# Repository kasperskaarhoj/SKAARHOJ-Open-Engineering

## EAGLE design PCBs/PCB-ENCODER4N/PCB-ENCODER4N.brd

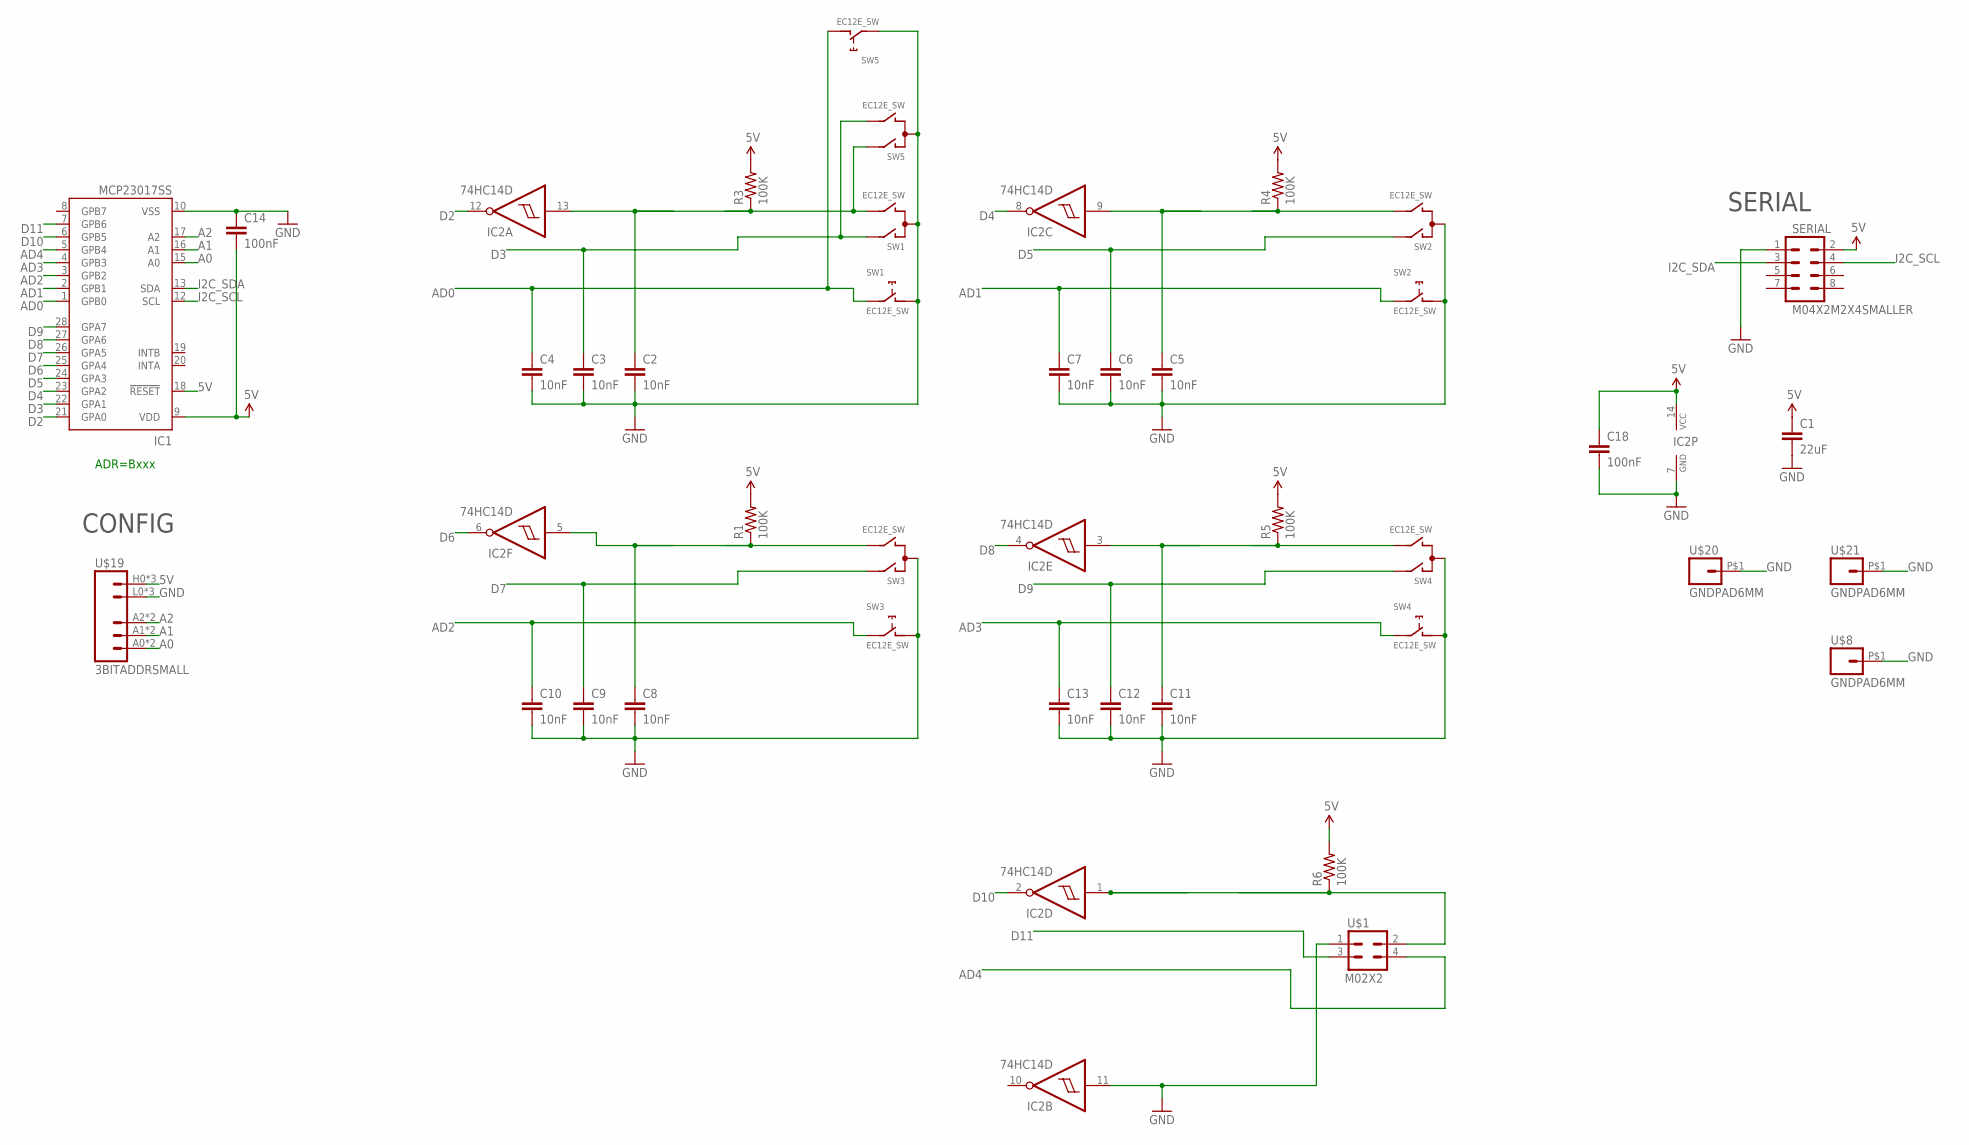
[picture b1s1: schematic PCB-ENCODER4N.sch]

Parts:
C1: 22uF; 0805
C2, C3, C4, C5, C6, C7, C8, C9, C10, C11, C12, C13: 10nF; 0603-CAP
C14, C18: 100nF; 0603-CAP
IC1: MCP23017SS; SSOP28; MPN MCP23017-E/SS
IC2: 74HC14D; SO14
R1, R3, R4, R5, R6: 100K; 0603-RES
SERIAL: M04X2M2X4SMALLER; M2X4SMALLER
SW1, SW2, SW3, SW4, SW5: EC12E_SW; ALPS_EC12E_SW
U$1: M02X2; 2X2
U$8, U$20, U$21: GNDPAD6MM; 3.2MMPAD6MM
U$19: 3BITADDRSMALL; 3BITADDR_SMALL

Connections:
5V: C1.1, C14.2, C18.1, IC1.9 (VDD), IC1.18 (!RESET), IC2.14 (VCC), R1.2, R3.2, R4.2, R5.2, R6.2, SERIAL.2, U$19.H0 (VCC), U$19.H1 (VCC), U$19.H2 (VCC)
A0: IC1.15 (A0), U$19.A0, U$19.AS0 (A0)
A1: IC1.16 (A1), U$19.A1, U$19.AS1 (A1)
A2: IC1.17 (A2), U$19.A2, U$19.AS2 (A2)
AD0: C4.1, IC1.1 (GPB0), SW1.E (2), SW5.D (1)
AD1: C7.1, IC1.2 (GPB1), SW2.E (2)
AD2: C10.1, IC1.3 (GPB2), SW3.E (2)
AD3: C13.1, IC1.4 (GPB3), SW4.E (2)
AD4: IC1.5 (GPB4), U$1.4
D2: IC1.21 (GPA0), IC2.12 (O)
D3: C3.1, IC1.22 (GPA1), SW1.A, SW5.B
D4: IC1.23 (GPA2), IC2.8 (O)
D5: C6.1, IC1.24 (GPA3), SW2.A
D6: IC1.25 (GPA4), IC2.6 (O)
D7: C9.1, IC1.26 (GPA5), SW3.A
D8: IC1.27 (GPA6), IC2.4 (O)
D9: C12.1, IC1.28 (GPA7), SW4.A
D10: IC1.6 (GPB5), IC2.2 (O)
D11: IC1.7 (GPB6), U$1.3
GND: C1.2, C2.2, C3.2, C4.2, C5.2, C6.2, C7.2, C8.2, C9.2, C10.2, C11.2, C12.2, C13.2, C14.1, C18.2, IC1.10 (VSS), IC2.7 (GND), IC2.11 (I), SERIAL.1, SW1.C, SW1.D (1), SW2.C, SW2.D (1), SW3.C, SW3.D (1), SW4.C, SW4.D (1), SW5.C, SW5.E (2), U$1.1, U$8.P$1, U$19.L0 (GND), U$19.L1 (GND), U$19.L2 (GND), U$20.P$1, U$21.P$1
I2C_SCL: IC1.12 (SCL), SERIAL.4
I2C_SDA: IC1.13 (SDA), SERIAL.3
unnamed: IC2.1 (I), R6.1, U$1.2
unnamed: C8.1, IC2.5 (I), R1.1, SW3.B
unnamed: C2.1, IC2.13 (I), R3.1, SW1.B, SW5.A
unnamed: C5.1, IC2.9 (I), R4.1, SW2.B
unnamed: C11.1, IC2.3 (I), R5.1, SW4.B

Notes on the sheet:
SERIAL
ADR=Bxxx
CONFIG

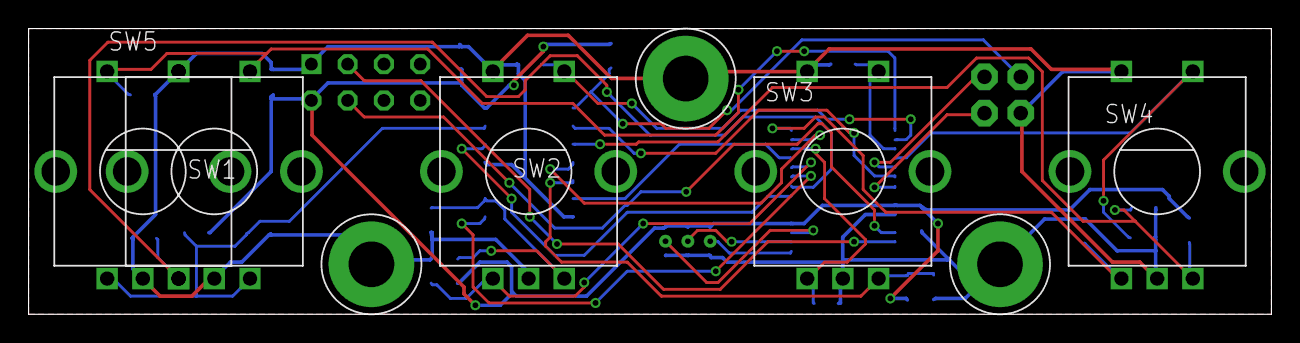
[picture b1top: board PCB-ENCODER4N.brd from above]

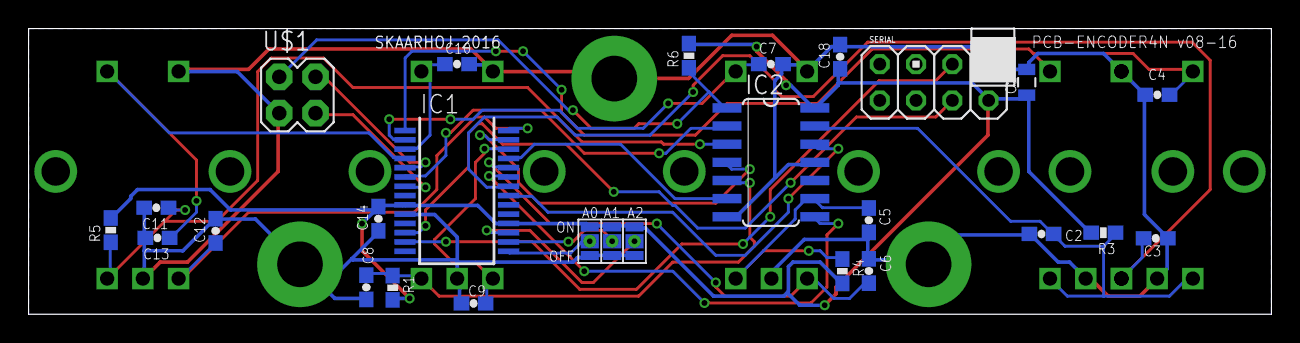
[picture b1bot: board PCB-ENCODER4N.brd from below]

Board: 2 copper layers, 87.0 x 20.0 mm, 33 parts (25 on the bottom side), 27 nets.

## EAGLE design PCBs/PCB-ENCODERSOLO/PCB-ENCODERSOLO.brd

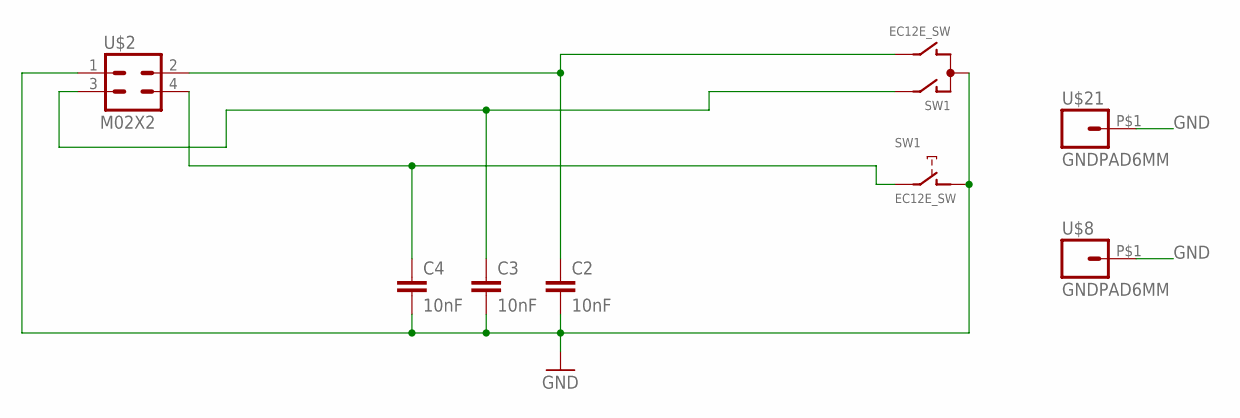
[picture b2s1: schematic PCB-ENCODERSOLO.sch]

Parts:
C2, C3, C4: 10nF; 0603-CAP
SW1: EC12E_SW; ALPS_EC12E_SW
U$2: M02X2; 2X2
U$8, U$21: GNDPAD6MM; 3.2MMPAD6MM

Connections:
AD0: C4.1, SW1.E (2), U$2.4
D3: C3.1, SW1.A, U$2.3
GND: C2.2, C3.2, C4.2, SW1.C, SW1.D (1), U$2.1, U$8.P$1, U$21.P$1
unnamed: C2.1, SW1.B, U$2.2

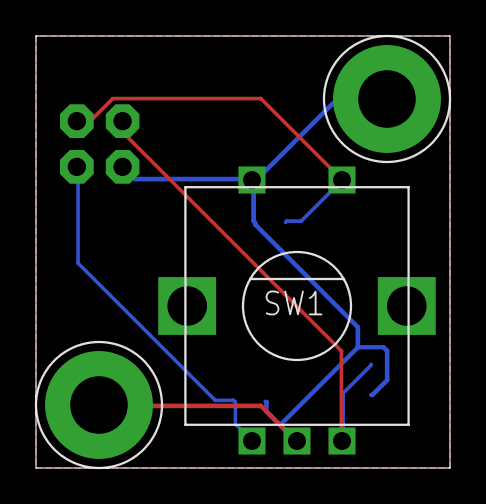
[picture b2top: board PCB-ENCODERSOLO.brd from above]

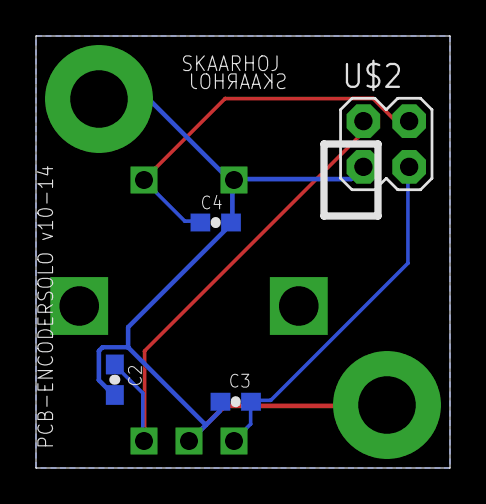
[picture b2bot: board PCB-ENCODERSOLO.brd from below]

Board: 2 copper layers, 23.0 x 24.0 mm, 7 parts (4 on the bottom side), 4 nets.

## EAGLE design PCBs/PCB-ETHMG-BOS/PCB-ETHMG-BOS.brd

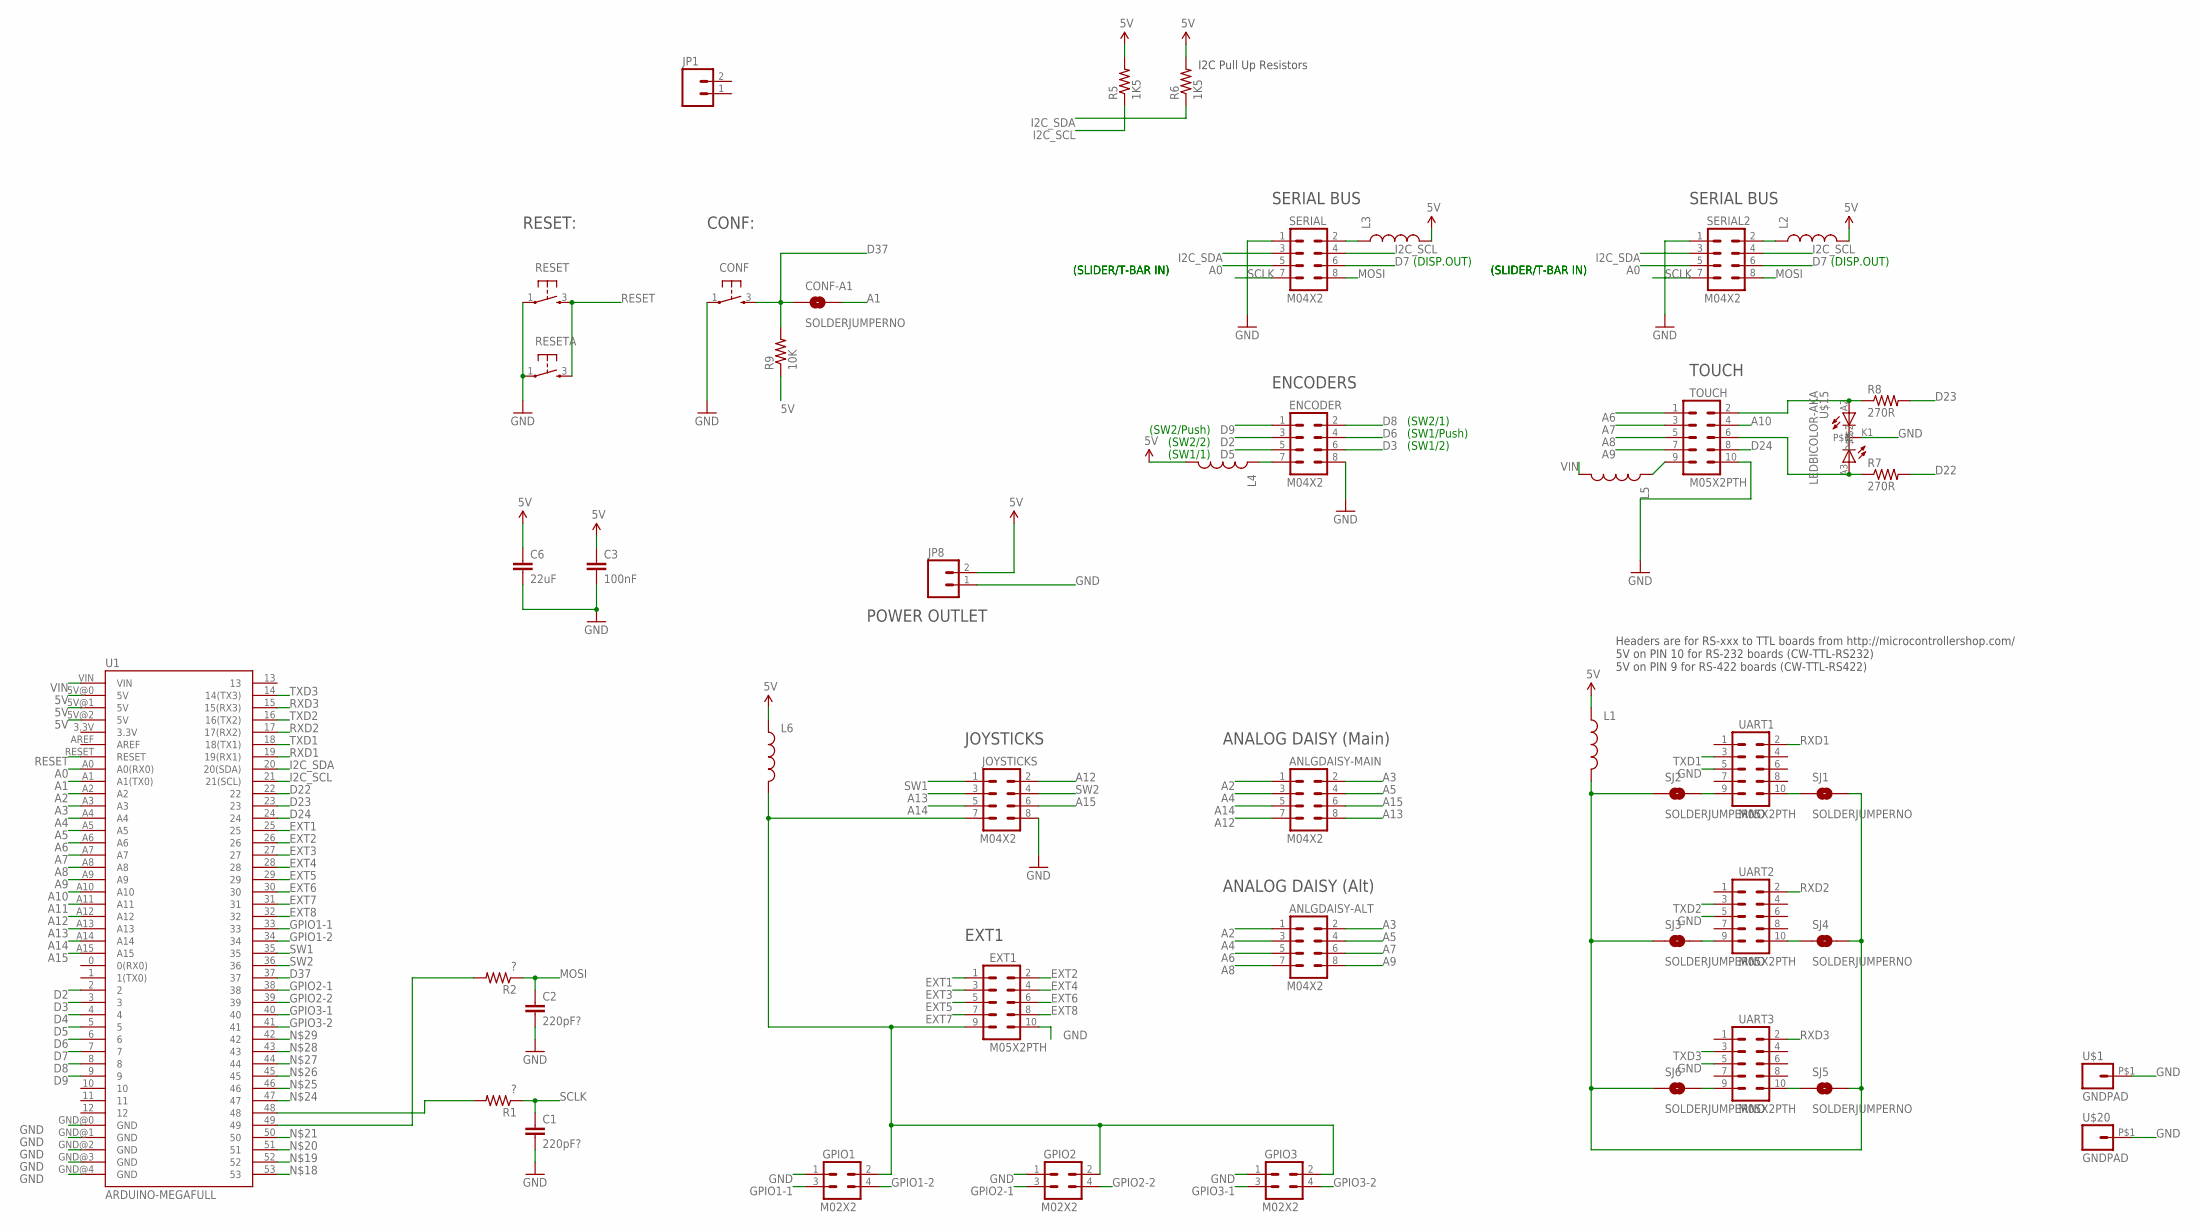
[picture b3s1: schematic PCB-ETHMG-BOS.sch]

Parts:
ANLGDAISY-ALT: M04X2; 2X4
ANLGDAISY-MAIN: M04X2; 2X4
C1, C2: 220pF?; 0603-CAP
C3: 100nF; 0603-CAP
C6: 22uF; 0805
CONF: TAC_SWITCH; PUSHBUTTON
CONF-A1: SOLDERJUMPERNO; SJ_2S-NO
ENCODER: M04X2; 2X4
EXT1: M05X2PTH; AVR_ICSP
GPIO1, GPIO2, GPIO3: M02X2; 2X2
JOYSTICKS: M04X2; 2X4
JP1: M02PTH; 1X02
JP8: M02PTH4; 1X02_XTRA_BIG
L1, L2, L3, L4, L5, L6: INDUCTOR0805; 0805
R1, R2: ?; 0603-RES
R5, R6: 1K5; 0603-RES
R7, R8: 270R; 0603-RES
R9: 10K; 0603-RES
RESET: TAC_SWITCH; PUSHBUTTON
RESETA: TAC_SWITCH; PUSHBUTTON
SERIAL, SERIAL2: M04X2; 2X4
SJ1, SJ2, SJ3, SJ4, SJ5, SJ6: SOLDERJUMPERNO; SJ_2S-NO
TOUCH: M05X2PTH; AVR_ICSP
U1: ARDUINO-MEGAFULL; ARDUINO_MEGA
U$1, U$20: GNDPAD; 3.2MMPAD
U$15: LEDBICOLOR-AKA; LED5MM-BICOLOR
UART1, UART2, UART3: M05X2PTH; AVR_ICSP

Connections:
5V: C3.1, C6.1, JP8.2, L1.1, L2.2, L3.2, L4.2, L6.1, R5.2, R6.2, R9.1, U1.5V@0 (5V), U1.5V@1 (5V), U1.5V@2 (5V)
A0: SERIAL.5, SERIAL2.5, U1.A0 (A0(RX0))
A1: CONF-A1.2, U1.A1 (A1(TX0))
A2: ANLGDAISY-ALT.1, ANLGDAISY-MAIN.1, U1.A2
A3: ANLGDAISY-ALT.2, ANLGDAISY-MAIN.2, U1.A3
A4: ANLGDAISY-ALT.3, ANLGDAISY-MAIN.3, U1.A4
A5: ANLGDAISY-ALT.4, ANLGDAISY-MAIN.4, U1.A5
A6: ANLGDAISY-ALT.5, TOUCH.1, U1.A6
A7: ANLGDAISY-ALT.6, TOUCH.3, U1.A7
A8: ANLGDAISY-ALT.7, TOUCH.5, U1.A8
A9: ANLGDAISY-ALT.8, TOUCH.7, U1.A9
A10: TOUCH.4, U1.A10
A11: U1.A11
A12: ANLGDAISY-MAIN.7, JOYSTICKS.2, U1.A12
A13: ANLGDAISY-MAIN.8, JOYSTICKS.3, U1.A13
A14: ANLGDAISY-MAIN.5, JOYSTICKS.5, U1.A14
A15: ANLGDAISY-MAIN.6, JOYSTICKS.6, U1.A15
D2: ENCODER.3, U1.2
D3: ENCODER.6, U1.3
D4: U1.4
D5: ENCODER.5, U1.5
D6: ENCODER.4, U1.6
D7: SERIAL.6, SERIAL2.6, U1.7
D8: ENCODER.2, U1.8
D9: ENCODER.1, U1.9
D22: R7.2, U1.22
D23: R8.2, U1.23
D24: TOUCH.8, U1.24
D37: CONF.3, CONF-A1.1, R9.2, U1.37
EXT1: EXT1.1, U1.25
EXT2: EXT1.2, U1.26
EXT3: EXT1.3, U1.27
EXT4: EXT1.4, U1.28
EXT5: EXT1.5, U1.29
EXT6: EXT1.6, U1.30
EXT7: EXT1.7, U1.31
EXT8: EXT1.8, U1.32
GND: C1.2, C2.2, C3.2, C6.2, CONF.1, ENCODER.8, EXT1.10, GPIO1.1, GPIO2.1, GPIO3.1, JOYSTICKS.8, JP8.1, RESET.1, RESETA.1, SERIAL.1, SERIAL2.1, TOUCH.10, U1.GND@0 (GND), U1.GND@1 (GND), U1.GND@2 (GND), U1.GND@3 (GND), U1.GND@4 (GND), U$1.P$1, U$15.K1, U$20.P$1, UART1.5, UART2.5, UART3.5
GPIO1-1: GPIO1.3, U1.33
GPIO1-2: GPIO1.4, U1.34
GPIO2-1: GPIO2.3, U1.38
GPIO2-2: GPIO2.4, U1.39
GPIO3-1: GPIO3.3, U1.40
GPIO3-2: GPIO3.4, U1.41
I2C_SCL: R5.1, SERIAL.4, SERIAL2.4, U1.21 (21(SCL))
I2C_SDA: R6.1, SERIAL.3, SERIAL2.3, U1.20 (20(SDA))
MOSI: C2.1, R2.1, SERIAL.8, SERIAL2.8
unnamed: L2.1, SERIAL2.2
unnamed: L3.1, SERIAL.2
unnamed: SJ6.2, UART3.9
unnamed: ENCODER.7, L4.1
unnamed: L5.1, TOUCH.9
unnamed: SJ3.2, UART2.9
unnamed: EXT1.9, GPIO1.2, GPIO2.2, GPIO3.2, JOYSTICKS.7, L6.2
unnamed: L1.2, SJ1.2, SJ2.1, SJ3.1, SJ4.2, SJ5.2, SJ6.1
unnamed: SJ2.2, UART1.9
unnamed: SJ1.1, UART1.10
unnamed: R1.2, U1.48
unnamed: SJ4.1, UART2.10
unnamed: SJ5.1, UART3.10
unnamed: R2.2, U1.49
unnamed: R8.1, TOUCH.2, U$15.A2
unnamed: R7.1, TOUCH.6, U$15.A3
RESET: RESET.3, RESETA.3, U1.RESET
RXD1: U1.19 (19(RX1)), UART1.2
RXD2: U1.17 (17(RX2)), UART2.2
RXD3: U1.15 (15(RX3)), UART3.2
SCLK: C1.1, R1.1, SERIAL.7, SERIAL2.7
SW1: JOYSTICKS.1, U1.35
SW2: JOYSTICKS.4, U1.36
TXD1: U1.18 (18(TX1)), UART1.3
TXD2: U1.16 (16(TX2)), UART2.3
TXD3: U1.14 (14(TX3)), UART3.3
VIN: L5.2, U1.VIN

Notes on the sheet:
JOYSTICKS
EXT1
Headers are for RS-xxx to TTL boards from http://microcontrollershop.com/ 5V on PIN 10 for RS-232 boards (CW-TTL-RS232) 5V on PIN 9 for RS-422 boards (CW-TTL-RS422)
I2C Pull Up Resistors
ENCODERS
SERIAL BUS
TOUCH
(SLIDER/T-BAR IN)
(SW2/Push)
(SW2/2)
(SW1/1)
(SW2/1)
(SW1/Push)
(SW1/2)
(DISP.OUT)
RESET:
CONF:
ANALOG DAISY (Main)
ANALOG DAISY (Alt)
POWER OUTLET

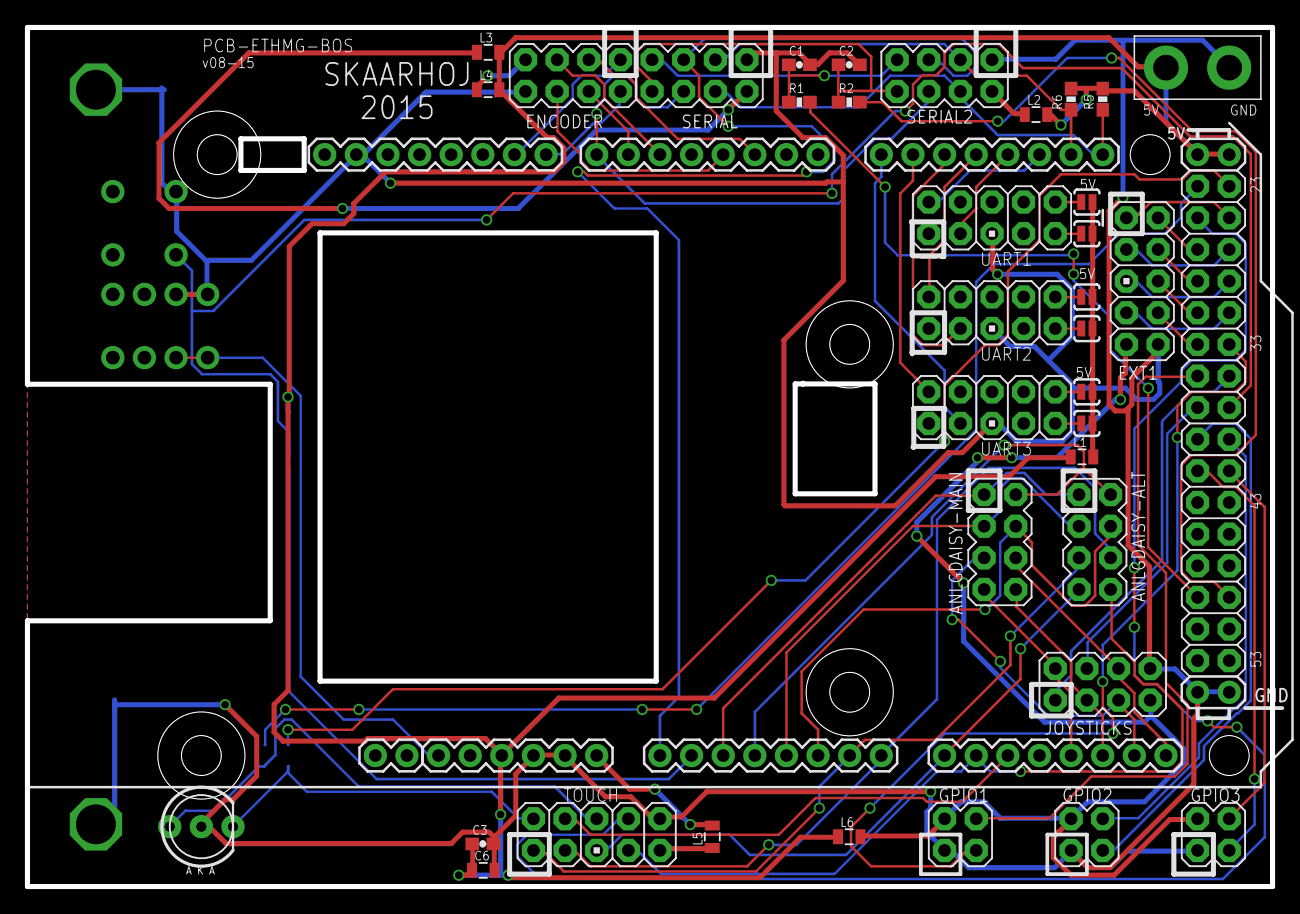
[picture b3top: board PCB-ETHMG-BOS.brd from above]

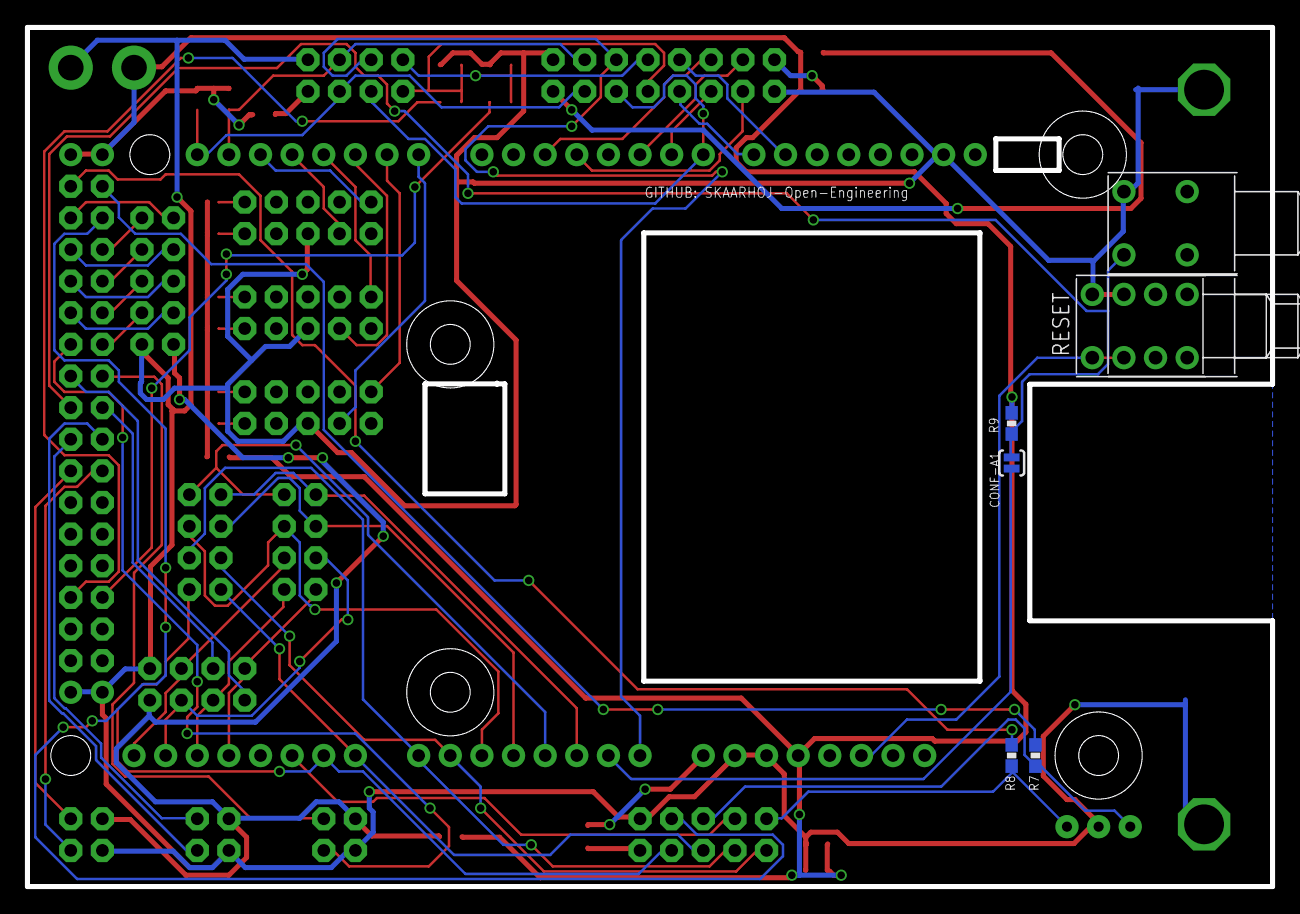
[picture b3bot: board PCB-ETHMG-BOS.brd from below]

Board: 2 copper layers, 100.0 x 69.0 mm, 47 parts (7 on the bottom side), 72 nets.

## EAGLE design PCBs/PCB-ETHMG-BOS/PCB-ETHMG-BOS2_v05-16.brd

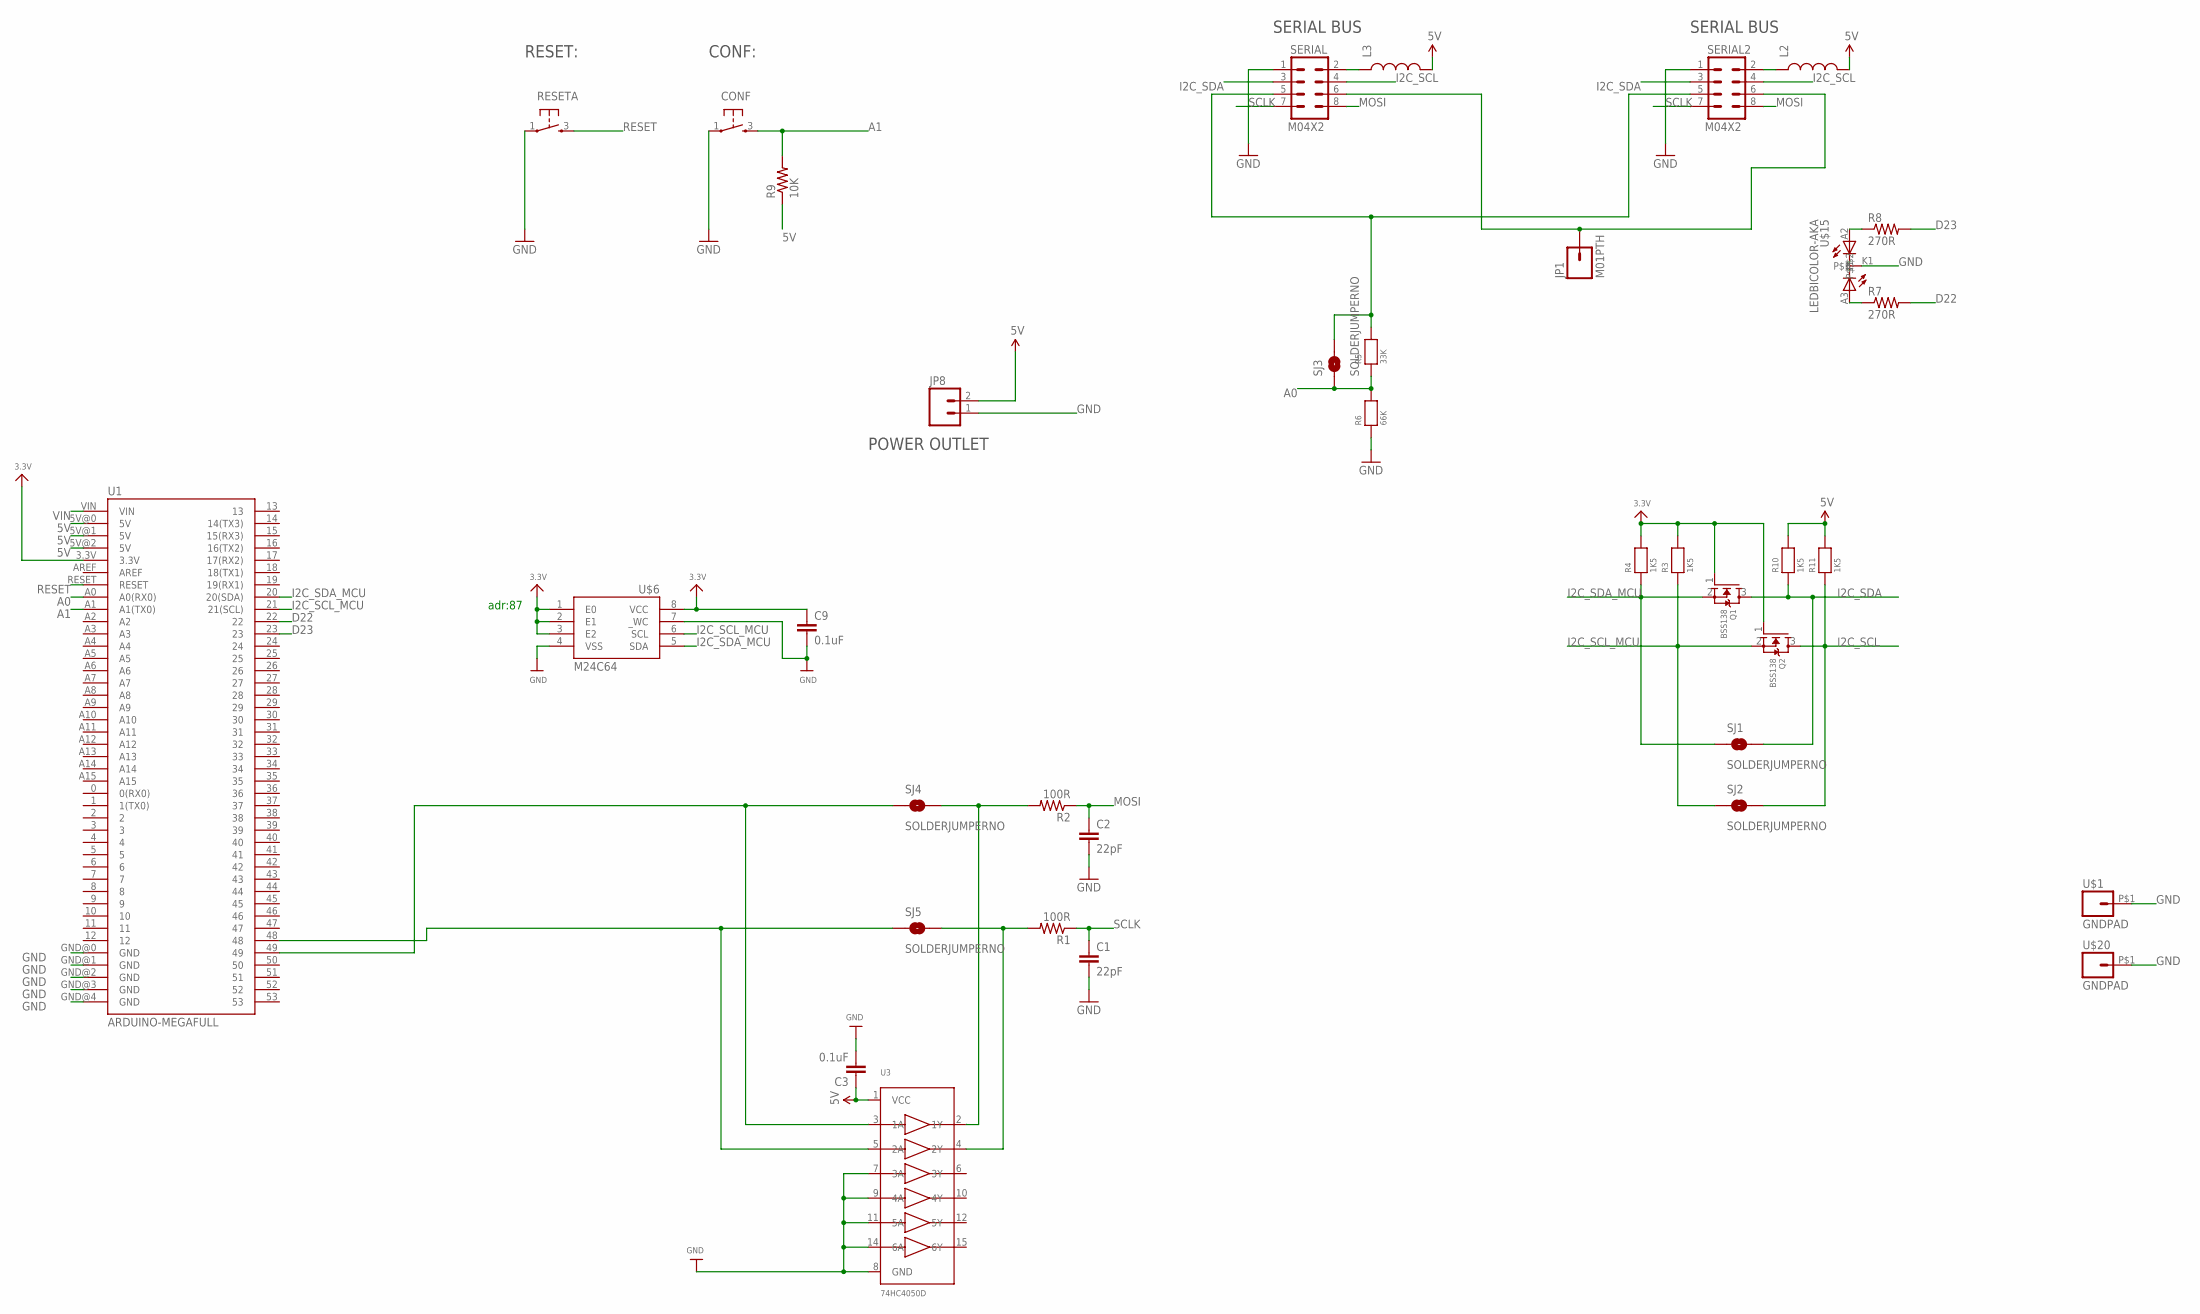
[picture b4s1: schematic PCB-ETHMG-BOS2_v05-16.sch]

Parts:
C1, C2: 22pF; 0603-CAP
C3, C9: 0.1uF; 0603-CAP
CONF: TAC_SWITCH; PUSHBUTTON
JP1: M01PTH; 1X01
JP8: M02PTH4; 1X02_XTRA_BIG
L2, L3: INDUCTOR0805; 0805
Q1, Q2: BSS138; SOT23-R
R1, R2: 100R; 0603-RES
R3, R4, R10, R11: 1K5; 0603
R5: 33K; 0603
R6: 66K; 0603
R7, R8: 270R; 0603-RES
R9: 10K; 0603-RES
RESETA: TAC_SWITCH; PUSHBUTTON
SERIAL, SERIAL2: M04X2; 2X4
SJ1, SJ2, SJ3, SJ4, SJ5: SOLDERJUMPERNO; SJ_2S-NO
U1: ARDUINO-MEGAFULL; ARDUINO_MEGA
U3: 74HC4050D; TSSOP16
U$1, U$20: GNDPAD; 3.2MMPAD
U$6: M24C64; TSSOP8
U$15: LEDBICOLOR-AKA; LED5MM-BICOLOR

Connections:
3.3V: C9.1, Q1.1 (G), Q2.1 (G), R3.2, R4.2, U1.3.3V, U$6.1 (E0), U$6.2 (E1), U$6.3 (E2), U$6.8 (VCC)
5V: C3.1, JP8.2, L2.2, L3.2, R9.1, R10.2, R11.2, U1.5V@0 (5V), U1.5V@1 (5V), U1.5V@2 (5V), U3.1 (VCC)
A0: R5.1, R6.2, SJ3.1, U1.A0 (A0(RX0))
A1: CONF.3, R9.2, U1.A1 (A1(TX0))
D22: R7.2, U1.22
D23: R8.2, U1.23
GND: C1.2, C2.2, C3.2, C9.2, CONF.1, JP8.1, R6.1, RESETA.1, SERIAL.1, SERIAL2.1, U1.GND@0 (GND), U1.GND@1 (GND), U1.GND@2 (GND), U1.GND@3 (GND), U1.GND@4 (GND), U3.7 (3A), U3.8 (GND), U3.9 (4A), U3.11 (5A), U3.14 (6A), U$1.P$1, U$6.4 (VSS), U$6.7 (_WC), U$15.K1, U$20.P$1
I2C_SCL: Q2.3 (D), R11.1, SERIAL.4, SERIAL2.4, SJ2.2
I2C_SCL_MCU: Q2.2 (S), R3.1, SJ2.1, U1.21 (21(SCL)), U$6.6 (SCL)
I2C_SDA: Q1.3 (D), R10.1, SERIAL.3, SERIAL2.3, SJ1.2
I2C_SDA_MCU: Q1.2 (S), R4.1, SJ1.1, U1.20 (20(SDA)), U$6.5 (SDA)
MOSI: C2.1, R2.1, SERIAL.8, SERIAL2.8
unnamed: L2.1, SERIAL2.2
unnamed: L3.1, SERIAL.2
unnamed: R5.2, SERIAL.5, SERIAL2.5, SJ3.2
unnamed: R2.2, SJ4.2, U3.2 (1Y)
unnamed: JP1.1, SERIAL.6, SERIAL2.6
unnamed: R1.2, SJ5.2, U3.4 (2Y)
unnamed: SJ4.1, U1.49, U3.3 (1A)
unnamed: R8.1, U$15.A2
unnamed: R7.1, U$15.A3
RESET: RESETA.3, U1.RESET
SCLK: C1.1, R1.1, SERIAL.7, SERIAL2.7
SCLK_3.3V: SJ5.1, U1.48, U3.5 (2A)
VIN: U1.VIN

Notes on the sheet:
SERIAL BUS
RESET:
CONF:
POWER OUTLET
adr:87

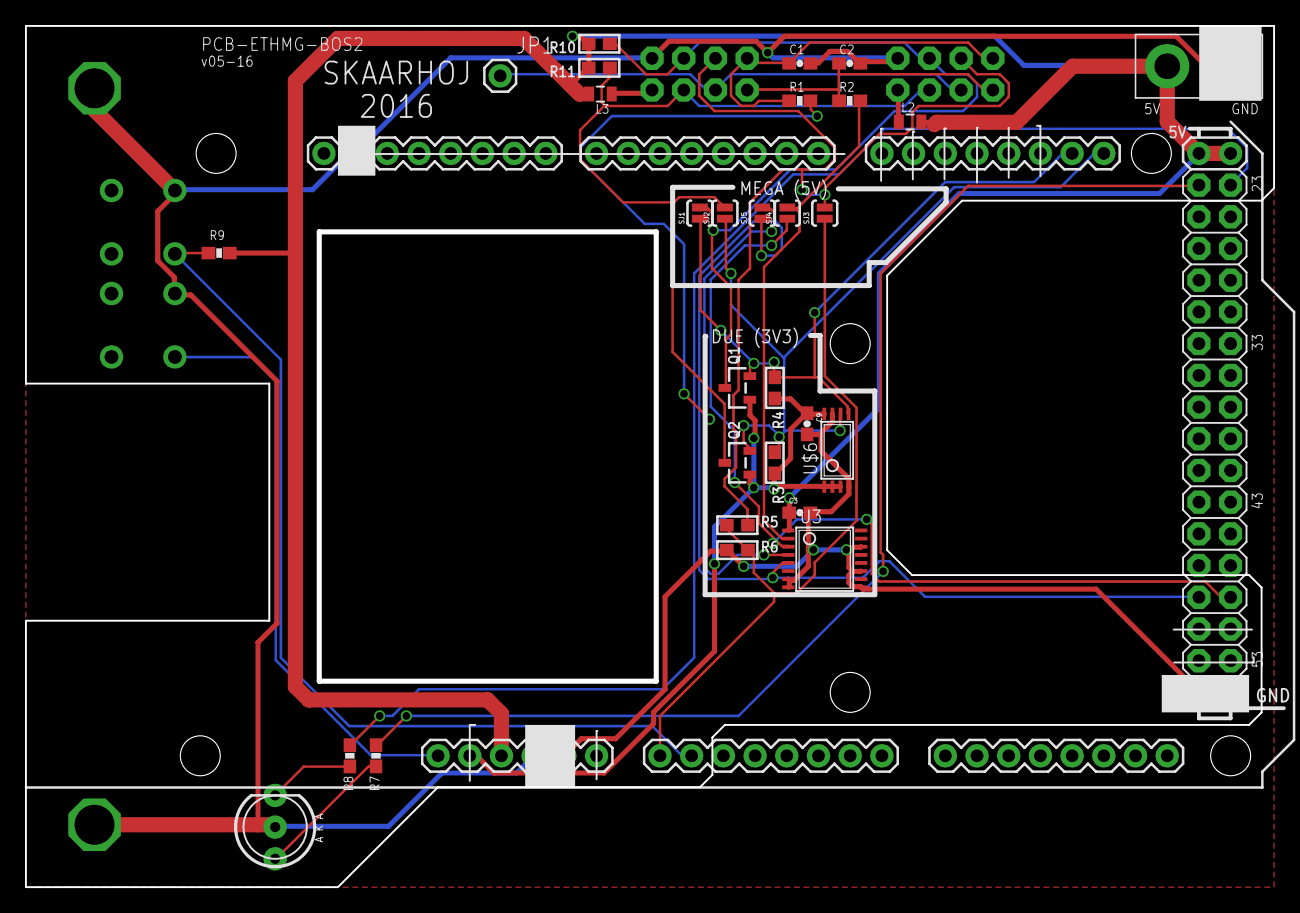
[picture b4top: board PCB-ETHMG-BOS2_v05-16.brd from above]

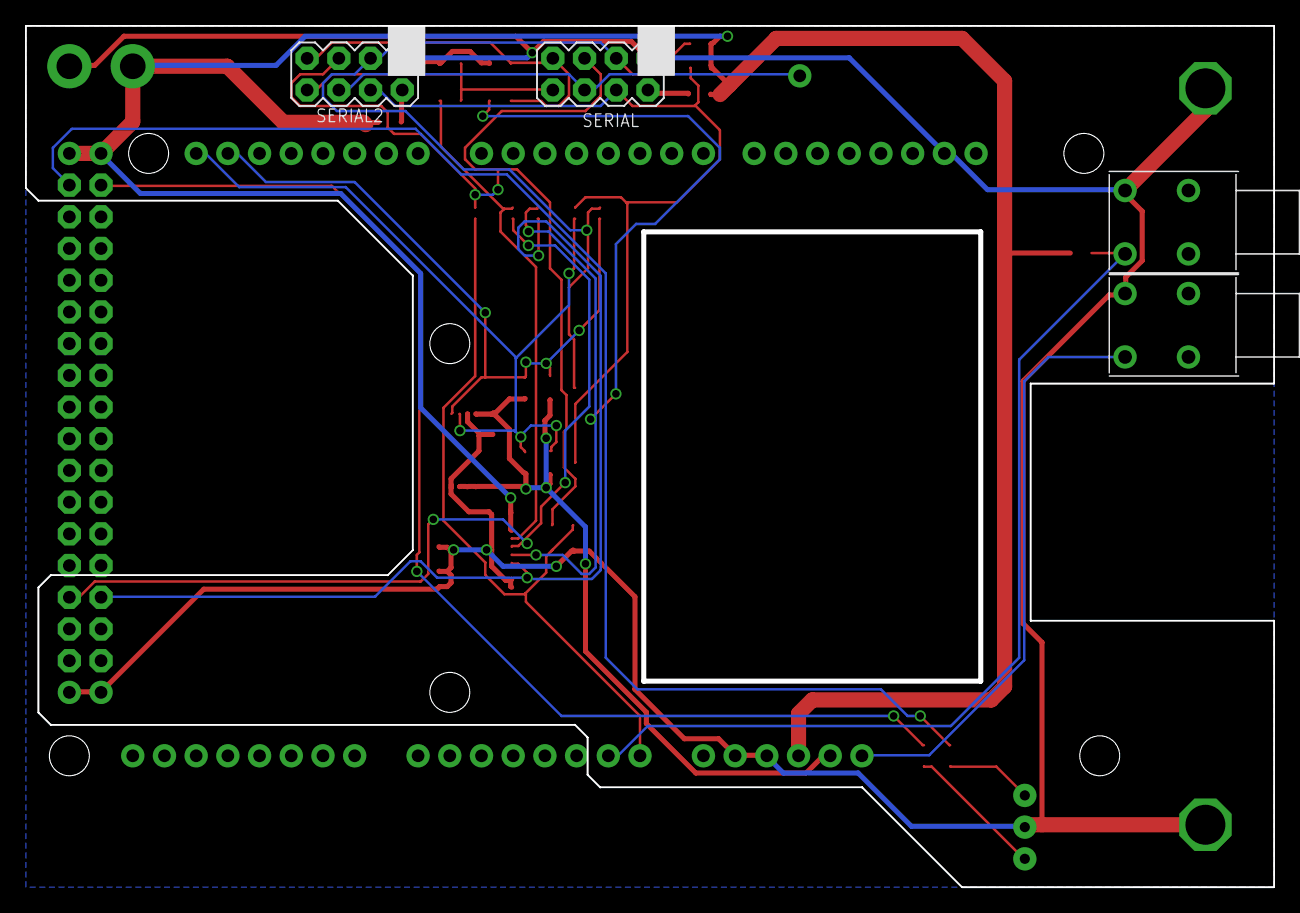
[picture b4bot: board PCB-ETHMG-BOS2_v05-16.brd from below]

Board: 2 copper layers, 100.0 x 69.0 mm, 36 parts (4 on the bottom side), 24 nets.

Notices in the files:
parts and their libraries:
SparkFun: Licensing: CC v3.0 Share-Alike You are welcome to use this library for commercial purposes.
